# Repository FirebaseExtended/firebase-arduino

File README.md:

# FirebaseArduino

This repo contains a collection of samples and an Arduino library that show how to call the [Firebase](https://www.firebase.com/) API from the [ESP8266 Arduino core](https://github.com/esp8266/Arduino).

## Status

This repository is no longer under active development. No new features will be added and issues are not actively triaged. Pull Requests which fix bugs are welcome and will be reviewed on a best-effort basis.

If you maintain a fork of this repository that you believe is healthier than the official version, we may consider recommending your fork. Please open a Pull Request if you believe that is the case.

## Samples

- [FirebaseDemo](https://github.com/googlesamples/firebase-arduino/tree/master/examples/FirebaseDemo_ESP8266) - shows the FirebaseArduino API methods.
- [FirebaseRoom](https://github.com/googlesamples/firebase-arduino/tree/master/examples/FirebaseRoom_ESP8266) - shows how to push sensor data and trigger actuator from Firebase.
- [FirebaseStream](https://github.com/googlesamples/firebase-arduino/tree/master/examples/FirebaseStream_ESP8266) - shows the FirebaseArduino streaming API.
- [FirebaseNeoPixel](https://github.com/googlesamples/firebase-arduino/tree/master/examples/FirebaseNeoPixel_ESP8266) - shows how to control an array of LEDs from a Firebase web app. 

## Documentation

- [FirebaseArduino API Reference](http://firebase-arduino.readthedocs.io/)

## Dependencies
- FirebaseArduino now depends on [ArduinoJson library](https://github.com/bblanchon/ArduinoJson) instead of containing it's own version of it. Please either use Library Manager or download specific version of the library from github. We recommend that ArduinoJson is at least version [5.13.1](https://github.com/bblanchon/ArduinoJson/tree/v5.13.1)

- ESP8266 Core SDK. We recommend using officially tagged releases and it should be at least [2.4.1](https://github.com/esp8266/Arduino/tree/2.4.1)

## Note for Handling Fingerprint Errors

If you encounter a fingerprint error, you can update the fingerprint in the `FirebaseHttpClient.h` file located at `Documents > Arduino > libraries > FirebaseArduino > src > FirebaseHttpClient.h`. Update the fingerprint to the latest one by visiting [this link](https://www.grc.com/fingerprints.htm).

## Disclaimer

*This is not an official Google product*.

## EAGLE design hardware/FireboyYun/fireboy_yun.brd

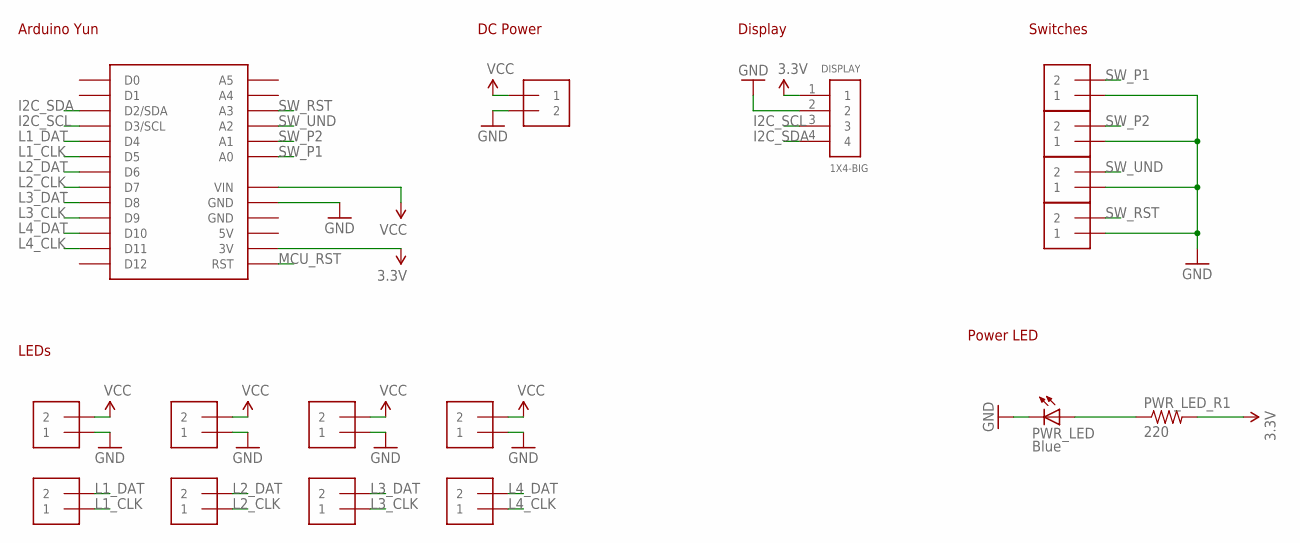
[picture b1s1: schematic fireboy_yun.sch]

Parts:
DC_5V_8A: 1X2-3.5MM
DISPLAY: 1X4-BIG; 1X04-BIG
L1_IO, L1_PWR, L2_IO, L2_PWR, L3_IO, L3_PWR, L4_IO, L4_PWR: 1X2-3.5MM
PWR_LED: Blue; LED3MM
PWR_LED_R1: 220; AXIAL-0.3
SW_P1, SW_P2: 1X2-3.5MM
SW_RST: 1X2-3.5MM
SW_UND: 1X2-3.5MM
YUN: YUN_MINI_SHIELD-BPLACE; YUN_MINI_SHIELD

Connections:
3.3V: DISPLAY.1, PWR_LED_R1.P$2 (2), YUN.3V
5V: YUN.5V
GND: DC_5V_8A.2, DISPLAY.2, L1_PWR.1, L2_PWR.1, L3_PWR.1, L4_PWR.1, PWR_LED.K (C), SW_P1.1, SW_P2.1, SW_RST.1, SW_UND.1, YUN.GND1 (GND), YUN.GND2 (GND)
I2C_SCL: DISPLAY.3, YUN.D3 (D3/SCL)
I2C_SDA: DISPLAY.4, YUN.D2 (D2/SDA)
L1_CLK: L1_IO.1, YUN.D5
L1_DAT: L1_IO.2, YUN.D4
L2_CLK: L2_IO.1, YUN.D7
L2_DAT: L2_IO.2, YUN.D6
L3_CLK: L3_IO.1, YUN.D9
L3_DAT: L3_IO.2, YUN.D8
L4_CLK: L4_IO.1, YUN.D11
L4_DAT: L4_IO.2, YUN.D10
MCU_RST: YUN.RESET (RST)
PWR_LED_R: PWR_LED.A, PWR_LED_R1.P$1 (1)
SW_P1: SW_P1.2, YUN.A0
SW_P2: SW_P2.2, YUN.A1
SW_RST: SW_RST.2, YUN.A3
SW_UND: SW_UND.2, YUN.A2
VCC: DC_5V_8A.1, L1_PWR.2, L2_PWR.2, L3_PWR.2, L4_PWR.2, YUN.VIN

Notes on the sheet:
Arduino Yun
LEDs
DC Power
Display
Switches
Power LED

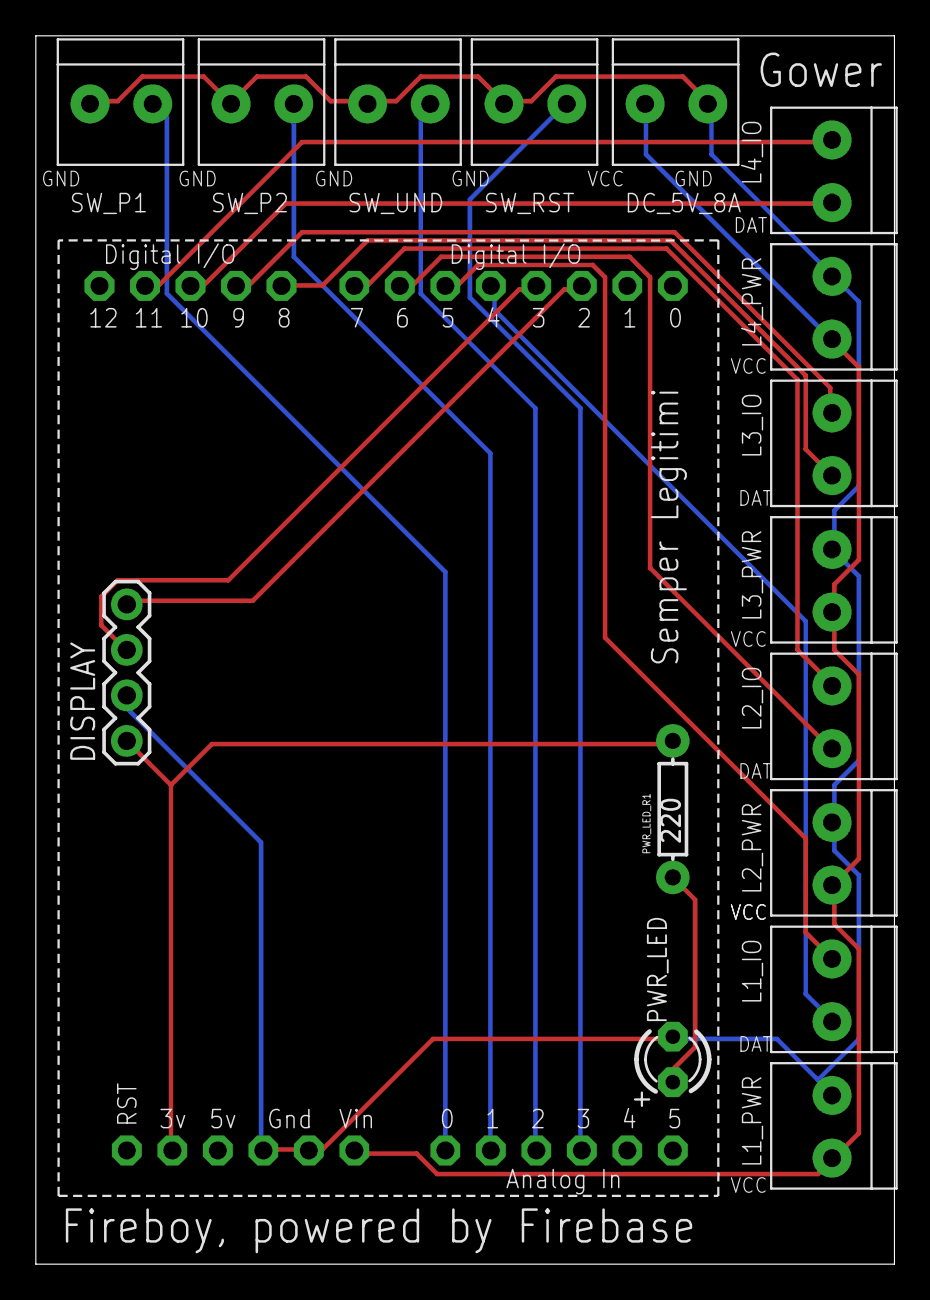
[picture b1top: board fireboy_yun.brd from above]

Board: 2 copper layers, 47.9 x 68.6 mm, 17 parts (0 on the bottom side), 18 nets.

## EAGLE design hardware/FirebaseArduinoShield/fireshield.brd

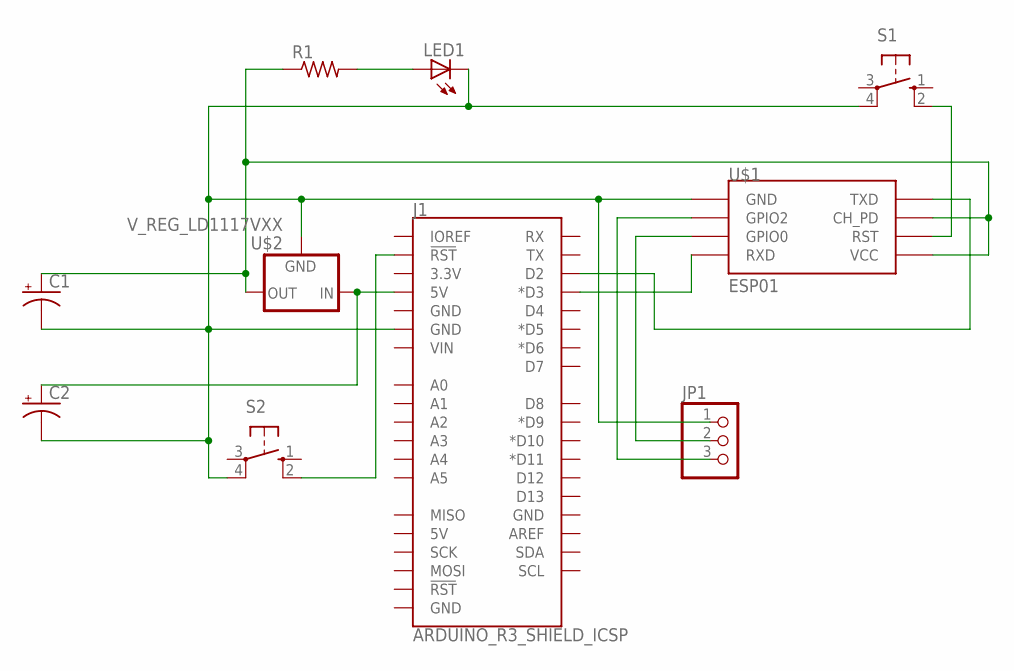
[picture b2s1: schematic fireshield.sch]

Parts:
C1, C2: 10UF-25V-20%(PTH)KIT; CPOL-RADIAL-10UF-25V-KIT
J1: ARDUINO_R3_SHIELD_ICSP; UNO_R3_SHIELD_ICSP
JP1: PINHD-1X3; 1X03
LED1: LED3MM
R1: R-US_0207/10; 0207/10
S1, S2: 10-XX; B3F-10XX
U$1: ESP01
U$2: V_REG_LD1117VXX; 78XXL

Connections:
unnamed: C1.2 (-), C2.2 (-), J1.GND@1 (GND), JP1.1, LED1.K (C), S1.4 (P1), S2.4 (P1), U$1.GND, U$2.IN (GND)
unnamed: J1.D3 (*D3), U$1.RX (RXD)
unnamed: C2.1 (+), J1.5V, U$2.OUT (IN)
unnamed: C1.1 (+), R1.1, U$1.CH_PD, U$1.VCC, U$2.GND (OUT)
unnamed: J1.D2, U$1.TX (TXD)
unnamed: S1.2 (S1), U$1.RST
unnamed: LED1.A, R1.2
unnamed: J1.RES (!RST!), S2.2 (S1)
unnamed: JP1.3, U$1.GPIO2
unnamed: JP1.2, U$1.GPIO0

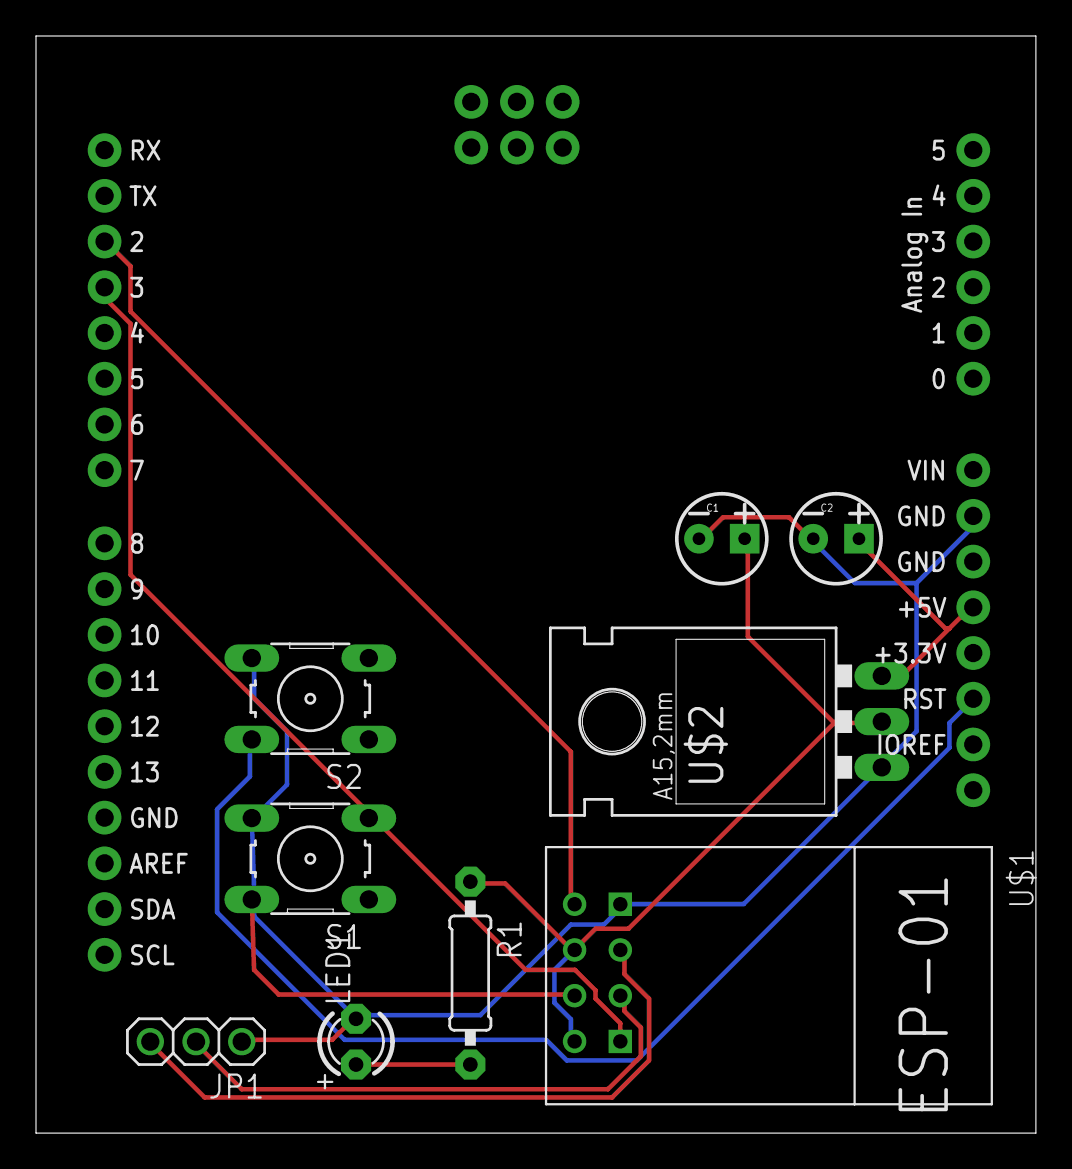
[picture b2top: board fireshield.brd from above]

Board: 2 copper layers, 55.5 x 61.0 mm, 10 parts (0 on the bottom side), 10 nets.

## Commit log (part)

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2016-04-15 Cleanup set test and add error test
2016-04-15 Added push command and test
2016-04-15 Added remove command and test
2016-04-15 Fixed all tests operating on the assumption that readLine() included the \r\n
2016-04-15 Add base for SerialTransciever.
2016-04-15 Getting serial example together
2016-04-15 All existing examples work now.
2016-04-15 Changes to make both arduino and tests compile
2016-04-15 Fixes to get FirebaseSerialHost.ino working!
2016-04-15 Switch to huzzah module.
2016-04-15 Added stream command using simple syntax.
2016-04-15 Reorganized the library to comply with arduino 1.5+ library standards https://github.com/arduino/Arduino/wiki/Arduino-IDE-1.5:-Library-specification
2016-04-15 Fixed some issues from PR review
2016-04-15 Fix parsing of returned json object.
2016-04-15 upgrade library to 1.5 style, import arduino-json-5.1.1 and start parsing json.
2016-04-15 Modem design image
2016-04-15 Untested initial command with tests Add tests
    Added gmock/gtest submodules
    Revert "Added gmock/gtest submodules"
    This reverts commit b975f3be8bfe28b92b6ebb31018bdae8b7857997.
    found out googlemock and googletest are now merged, only need one.
    Added googletest submodule
    Added *Ptr methods to firebase, get test mostly compiling
2016-04-15 Fixed some issues from PR review
    Modem design image
    modified diagram
    renamed diagram
    Create design.md
    Update design.md
    Updated diagram
2016-04-15 import test/
2016-04-15 import src/
2016-04-15 Get unit tests working with arduino json
2016-04-15 remove example from this branch
2016-04-16 add travis
2016-04-16 travis: language cpp + container
2016-04-16 travis: add compiler
2016-04-16 travis: add script
2016-04-16 travis: run test
2016-04-16 travis: before script export
2016-04-16 Revert "add travis integration"
2016-04-16 travis: fix esp8266 get.py invocation
2016-04-16 travis: remove after_install
2016-04-16 travis: fetch esp core
2016-04-16 travis: fix libraries symlinks
2016-04-16 travis: add staging and nightly
2016-04-16 travis: fix cwd
2016-04-16 firebase: fix ctors
2016-04-16 add typed get
    See #60.
2016-04-16 add typed push and set.
    See #60.
2016-04-22 Imported all from modem-impl2
2016-04-22 Added back auth() and fixed begin-command to use new Firebase constructor
2016-04-22 First attempt to add modem tests to travis
2016-04-22 Lets try c++
2016-04-22 Upgrade to trusty.
2016-04-26 third-party: bump arduino-json to 5.2
2016-04-26 third-party/arduino-json: restore string override ifdef guard
2016-04-26 attempt 2 to use apt.
2016-04-27 Add const modifier back to response().
    This broke the unit tests.
2016-04-27 travis: g++-4.8
2016-04-27 FirebaseArduino: fix error check
2016-04-27 example/FirebasePush: update example to loop
2016-04-27 examples/FirebaseDemo: fix error message
2016-04-27 examples/FirebaseDemo: fix demo
2016-04-27 examples/FirebaseDemo: add missing var and update doc
2016-04-29 Add virtual destructors now that we have virtual methods.
2016-04-29 Add Serial host to travis
2016-04-29 other ino needs to be it's own line
2016-04-29 create symlink for SoftwareSerial
2016-04-29 Add other examples to travis
2016-04-29 Added Adafruit_SSD1306 lib
2016-04-29 Fixed examples
2016-04-29 move all arduino libraries to releases instead of master
2016-04-29 minor fix
2016-04-29 travis: clean up
2016-04-30 README: cleanup
    - update sample name
    - add travis badge
    - update arduino version
2016-05-04 third-party/arduino-json: bump to 5.3
2016-05-04 third-party/arduino-json: apply string override patch
2016-05-04 FirebaseObject: include arduino-json-5.3
2016-05-06 Added other init types and fixed all examples.
2016-05-06 Fixed examples again
2016-05-06 Revert "Fixed String& -> char*"
    This reverts commit e721c8077a25b056f0ee2717f1a1c8d9d20f35fc.
    Eh I think we still want the String&, going to use c_str()
2016-05-06 Added comments to arduino api.
2016-05-06 Minor comment update
2016-05-07 Add top level readme and presumably metadata needed for ReadTheDocs to run.
2016-05-07 FirebaseObject: guard FIREBASE_JSONBUFFER_SIZE
2016-05-11 Comment updates from PR review.
2016-05-12 Added ReadTheDocs badge.
2016-05-13 Switch to using const ints for example
2016-05-14 Add another data to parsing.
2016-05-14 Change library name and add description.
2016-05-14 Support both string types in FirebaseArduino.h
2016-05-14 fixed typo
2016-05-15 examples/FirebaseRoom/README: add grove links
2016-05-15 FirebaseObject: simplify API
    - remove cast operator
    - remove indexing method
    - accept a subpath
2016-05-15 FirebaseObject: expose getJsonVariant
2016-05-15 FirebaseArduino: fix get methods signature
2016-05-15 examples: fix stream FirebaseObject usage
2016-05-15 FirebaseArduino: add typed push and set variant
    Fixes #140.
2016-05-15 Remove const char* methods
2016-05-15 examples/README: fix typos
2016-05-15 README: add versioning disclaimer, link to samples
2016-05-15 Fixed Neopixel
2016-05-16 FirebaseArduino: capitalize doc strings
2016-05-16 updated all examples
2016-05-16 fixed missnaming
2016-05-17 examples: rename neopixel directory
2016-05-17 examples/FirebaseNeoPixel: update to new API
    - remove colors_ext.h deps
2016-05-17 examples/*/README: remove trailing periods
2016-05-17 examples/FirebaseNeoPixel: fix begin call and rebase
2016-05-17 examples/FirebaseNeoPixel: update readme
2016-05-17 examples: update READMEs
2016-05-18 Started morse example
2016-05-19 README.st: nits
2016-05-19 README: add link to NeoPixel demo
2016-05-20 clean up timing
2016-05-21 Added onscreen indicators
2016-05-23 trigger github update
2016-05-23 Fix letter break timing
2016-05-24 Disable wifi, we don't use it yet.
2016-05-26 Restore FirebaseObject.h
2016-05-26 Bug fixes
2016-05-26 Fixs from testing streaming example
2016-05-26 Added code snippet that will allow strings to work for us until this is present upstream
2016-05-28 update the doc since the firebase UX changed
2016-06-01 Reverted Demo
2016-06-01 Add error handling to FirebaseDemo
2016-06-01 Added disconnect error
2016-06-03 Add json parsing to modem streaming
2016-06-07 update test with proper path.
2016-06-07 Fixed streaming test
2016-06-09 Added files that were lost
2016-06-17 Mention Sillicon Labs installing driver for OS X
2016-06-28 travis: bump arduino and esp core version
2016-07-03 firebaseobject: fix number decoding
2016-07-22 standardized on arduino String, builds for both tests and sketches now
2016-07-22 Register protocol in examples
2016-07-22 Cleanup BEGIN_DB rename
2016-07-29 Introduce working FirebaseCloudMessaging!
2016-07-29 Remove unused include in example
2016-08-19 First pass at serial protocol.
2016-08-19 Add Send_Message command.
2016-08-23 Firethings 1.3 schematics and board.
2016-08-24 hardware/firethings: fix relative paths
2016-08-24 Make kicad config more generic
2016-08-26 Abbreviate Message to MSG.
2016-08-26 Add argument comment to BEGIN_MSG and add usage info to MSG
2016-08-26 Update serial_protocol.md
    Addition doc changes
2016-09-26 examples/FirebaseRoom: link driver for Windows
2016-10-05 bump arduino-json to 5.6.7
    force arduino string in ArduinoJson
2016-10-18 Added warning message to stream() until we can fix it.
2016-10-28 Stop stream when we set value to avoid memory issues. Added example.
2016-10-28 Bug fixes, update ArduinoJson path, added base path for updates
2016-10-28 Make init match standard init for example
2016-10-28 Working portal
2016-10-28 merged other changes
2016-10-28 Updates the Web app to work with the new Firebase library
2016-11-01 Updates README
2016-11-04 Added network scanning to config page.
2016-11-05 Stop transcriber from trying to do anything if the wifi is not connected, unsupported state.
2016-11-17 Updates for consistency in example URIs
2016-11-18 Consistency for URI naming
2016-11-21 Fixes for template checks
2016-11-23 README: update travis badge url
2016-12-03 Add FireThing, main class for project. Includes config storage and retrieval from eeprom.
2016-12-03 Fix for travis test without config variables
2016-12-03 back to what I know works
2016-12-05 Changed to mutable char* for reading config
2016-12-13 * Changed Serializer::Deserialize to a non-static method. * Fixed default config initialization. * Added Firething call to delete stored config.
2016-12-14 FirebaseHttpClient: update firebaseio fingerprint
2016-12-17 contrib: fix submodules
2016-12-17 contrib: reset submodules
2017-02-09 Fixed a code comment
2017-04-02 Update .gitinore.firebase-realtime-database-operation
2017-04-10 FirebaseHttpClient_Esp8266: fix trailing space
2017-04-25 The signature for Firebase seems to have changed
2017-07-14 Update FirebaseCloudMessaging.cpp
    fix for https: instead of http:
2017-07-20 Update README.md
    add ESP8266 side code changes
2017-08-18 updated the firebase sha1 fingerprint.
2017-11-02 FirebaseArduino: allow mixing stream and non-stream commands
    With this change non-streaming operation will stop the stream and
    reuse the underlying http client.
    Call FirebaseArduino::stream again in order to reuse the stream.
    Fixes: #48
2017-11-07 Crazy update to use shared_ptr and get rid of old ArduinoJson library and use latest one.
2017-11-11 Forgot to add symbolic link.
2017-11-11 And finally removing symbolic link created for json library previously shipped with repo.
2017-11-11 More fixes for contrib test to use external JSON library.
2017-11-12 Add back getPtr functions.
2017-11-12 add build.f_cpu preference
2017-11-13 Avoid crashes when .available() is called by detecting that underlying stream has closed.
2017-12-30 added update method (PATCH)
2018-01-22 Added section about ArduinoJson dependency
2018-04-11 Refactoring into on-demand classes and http connections
2018-04-11 Attempt to fix mocks
2018-04-12 Add mock response
2018-04-18 Fix modem contrib
2018-04-18 Remove dead code.
2018-04-18 fix param definition in mock-firebase.h
2018-04-18 Fix error() mock definition
2018-04-18 fix error empty checks, header files and makefile for modem test
2018-05-06 fixing compilation and some of the tests. disabled stream test for now
2018-05-07 Enabling and fix stream unit test for modem code
2018-06-21 remove duplicates (#2)
2018-06-21 Removed temp files
2018-08-02 Updating firebase fingerprint
    The fingerprint changed on 2 Aug 2018.
    This is the new fingerprint
2018-08-15 Use proper API
2018-08-15 Try with explicit objects
2018-08-15 Checking tests with latest ArduinoJson lib version
2018-08-15 Maybe...
2018-08-15 Another test...
2018-08-15 Test with ESP8266 2.4.1
2018-08-15 Revert "Test with ESP8266 2.4.1"
    This reverts commit 728dd9d57ae6e714b36c5b0e015ac0879c7e4a84.
2018-08-15 Revert "Quick final test"
    This reverts commit db8456913a645b8f8ca37dcf6be9ab141d207ebd.
2018-08-15 Integrated feedback
2018-11-20 [FirebaseObject] Error message is never reset #390 (#391)
2019-01-25 Fix issue #388 ESP8266 fails to reconnect to FIREBASE #388 https://github.com/FirebaseExtended/firebase-arduino/issues/388
2019-03-02 New fingerprint update
2019-03-14 Added example
2019-04-18 Update to latest prod fingerprint
2019-04-18 Update to latest RTDB SSL fingerprint
2019-04-19 Update to latest RTDB SSL fingerprint (#438)
2019-06-17 Change in finger print
2019-10-04 ADD translate for PT-BR
    Readme.md translation into PT-BR
2019-11-24 Update FirebaseHttpClient.h
    finger print problem comming while connecting google firebase
2020-08-07 Update README.md (#498)
2021-03-06 Embed ArduinoJson 5.13.5 (fixes #426, fixes #444, fixes #484)
2021-10-28 Changing fingerprint to a working one
    I have tested and now the lib works for me
2022-04-04 Update fingerprint
2022-05-19 Update FirebaseHttpClient.h
    I have changed the kfirebase fingerprint to latest one 2022
2022-12-25 Updated realtime database domain fingerprint
2023-06-15 SSL Fingerprint Update Of letest 2023

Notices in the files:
parts and their libraries:
SparkFun-Boards: Licensing: Creative Commons ShareAlike 4.0 International - https://creativecommons.org/licenses/by-sa/4.0
